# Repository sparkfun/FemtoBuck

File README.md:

FemtoBuck LED Driver
===================  
](https://cdn.sparkfun.com/assets/parts/1/1/2/1/0/13716-01.jpg) 
 
[*FemtoBuck LED Driver (COM-13716)*](https://www.sparkfun.com/products/13716) 

This breakout board allows you to dim a single high-power channel of LEDs from 0-330mA, or 0-660mA (depending on the setting of a solder jumper), at up to 36V. 
Dimming control can be either via PWM or via analog signal from 0-2.5V.

Repository Contents
-------------------
* **/Hardware** - All Eagle design files (.brd, .sch)
* **/Production** - Test bed files and production panel files

Documentation
--------------
* **[Hookup Guide](https://learn.sparkfun.com/tutorials/femtobuck-constant-current-led-driver-hookup-guide)** - Basic hookup guide for the FemtoBuck.
* **[SparkFun Fritzing repo](https://github.com/sparkfun/Fritzing_Parts)** - Fritzing diagrams for SparkFun products.
* **[SparkFun 3D Model repo](https://github.com/sparkfun/3D_Models)** - 3D models of SparkFun products. 

Product Versions
----------------
* [COM-13716](https://www.sparkfun.com/products/13716)- Version 1.2. Currently for sale. 
* [COM-12937] (https://www.sparkfun.com/products/12937)- Version 1.0. Retired. 

Version History
---------------
* [V_1.2](https://github.com/sparkfun/FemtoBuck/tree/V_1.2) - GitHub files for version 1.2. 
* [V_1.0](https://github.com/sparkfun/FemtoBuck/tree/v_10) - GitHub files for version 1.0. 

License Information
-------------------

This product is _**open source**_! 

Please review the LICENSE.md file for license information. 

If you have any questions or concerns on licensing, please contact techsupport@sparkfun.com.

Distributed as-is; no warranty is given.

- Your friends at SparkFun.

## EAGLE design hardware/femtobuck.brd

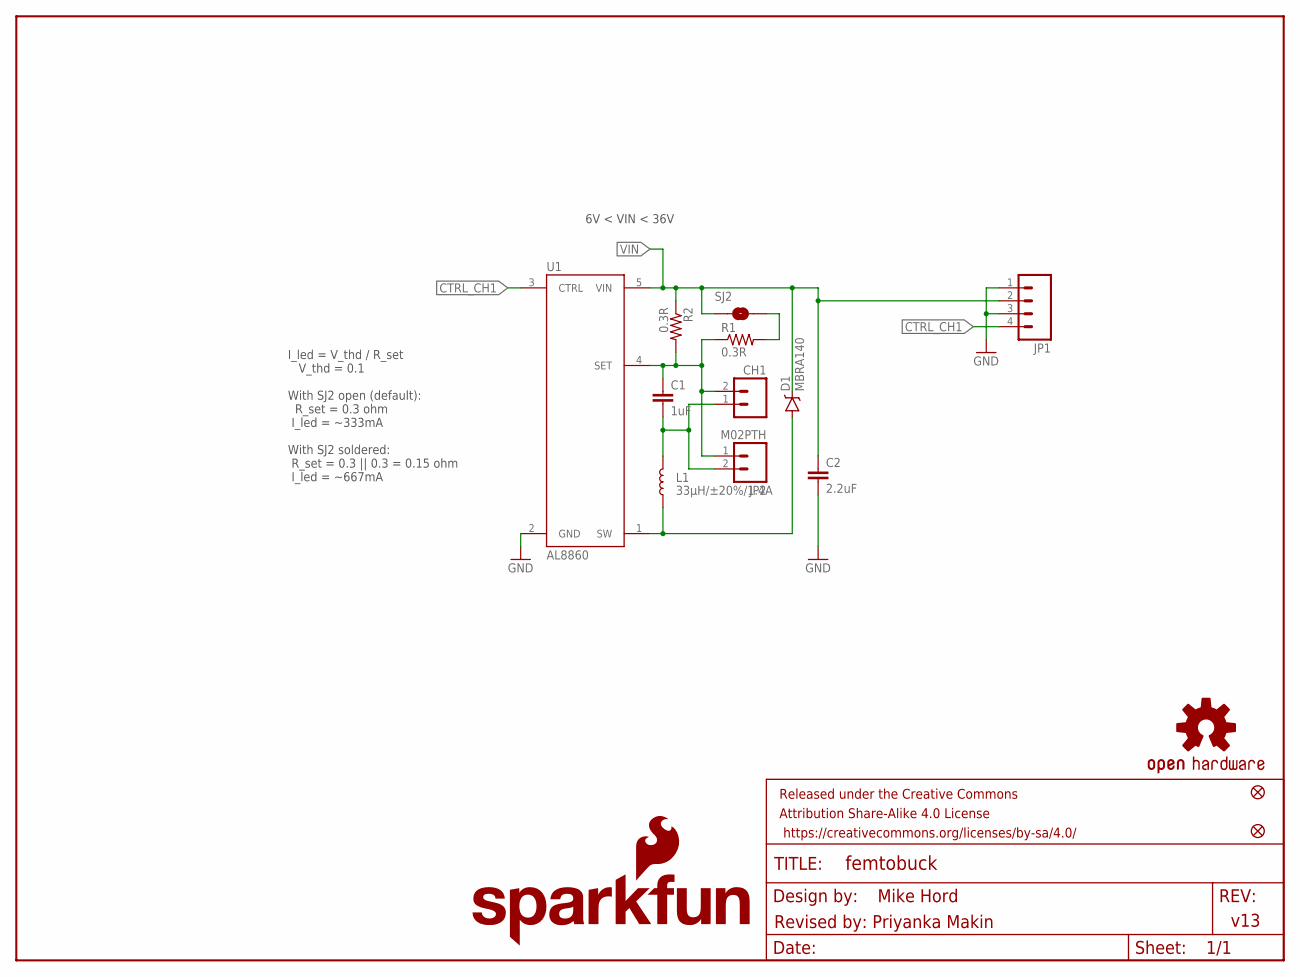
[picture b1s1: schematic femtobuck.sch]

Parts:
C1: 1uF; 1206-CAP
C2: 2.2uF; 1206-CAP
CH1: CONN_023.5MM_LOCK; SCREWTERMINAL-3.5MM-2_LOCK
D1: MBRA140; SMA-DIODE
FID1, FID2: FIDUCIAL1X2; FIDUCIAL-1X2
FRAME1: FRAME-LETTER; CREATIVE_COMMONS
JP1: M04PTH; 1X04
JP2: M02PTH; 1X02@1
L1: 33µH/±20%/1.4A; SRN6045
LOGO1: OSHW-LOGOS; OSHW-LOGO-S
LOGO2: SFE_LOGO_NAME_FLAME.1_INCH; SFE_LOGO_NAME_FLAME_.1
R1, R2: 0.3R; 0805
SJ2: NO Jumper; SMT-JUMPER_2_NO_NO-SILK
U1: AL8860; SOT23-5

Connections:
CTRL_CH1: JP1.4, U1.3 (CTRL)
GND: C2.2, JP1.1, JP1.3, U1.2 (GND)
unnamed: R1.2, SJ2.2
OUT+: C1.1, CH1.2, JP2.1, R1.1, R2.2, U1.4 (SET)
OUT-: C1.2, CH1.1, JP2.2, L1.2
SW: D1.A, L1.1, U1.1 (SW)
VIN: C2.1, D1.C, JP1.2, R2.1, SJ2.1, U1.5 (VIN)

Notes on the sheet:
I_led = V_thd / R_set V_thd = 0.1 With SJ2 open (default): R_set = 0.3 ohm I_led = ~333mA With SJ2 soldered: R_set = 0.3 || 0.3 = 0.15 ohm I_led = ~667mA
v13
Mike Hord
6V < VIN < 36V
Revised by: Priyanka Makin

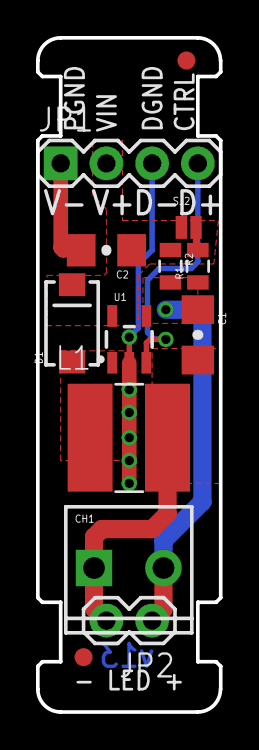
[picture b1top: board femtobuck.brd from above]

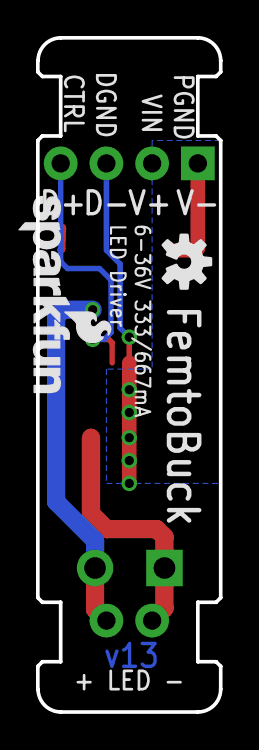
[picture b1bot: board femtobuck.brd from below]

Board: 2 copper layers, 10.2 x 37.5 mm, 16 parts (2 on the bottom side), 7 nets.

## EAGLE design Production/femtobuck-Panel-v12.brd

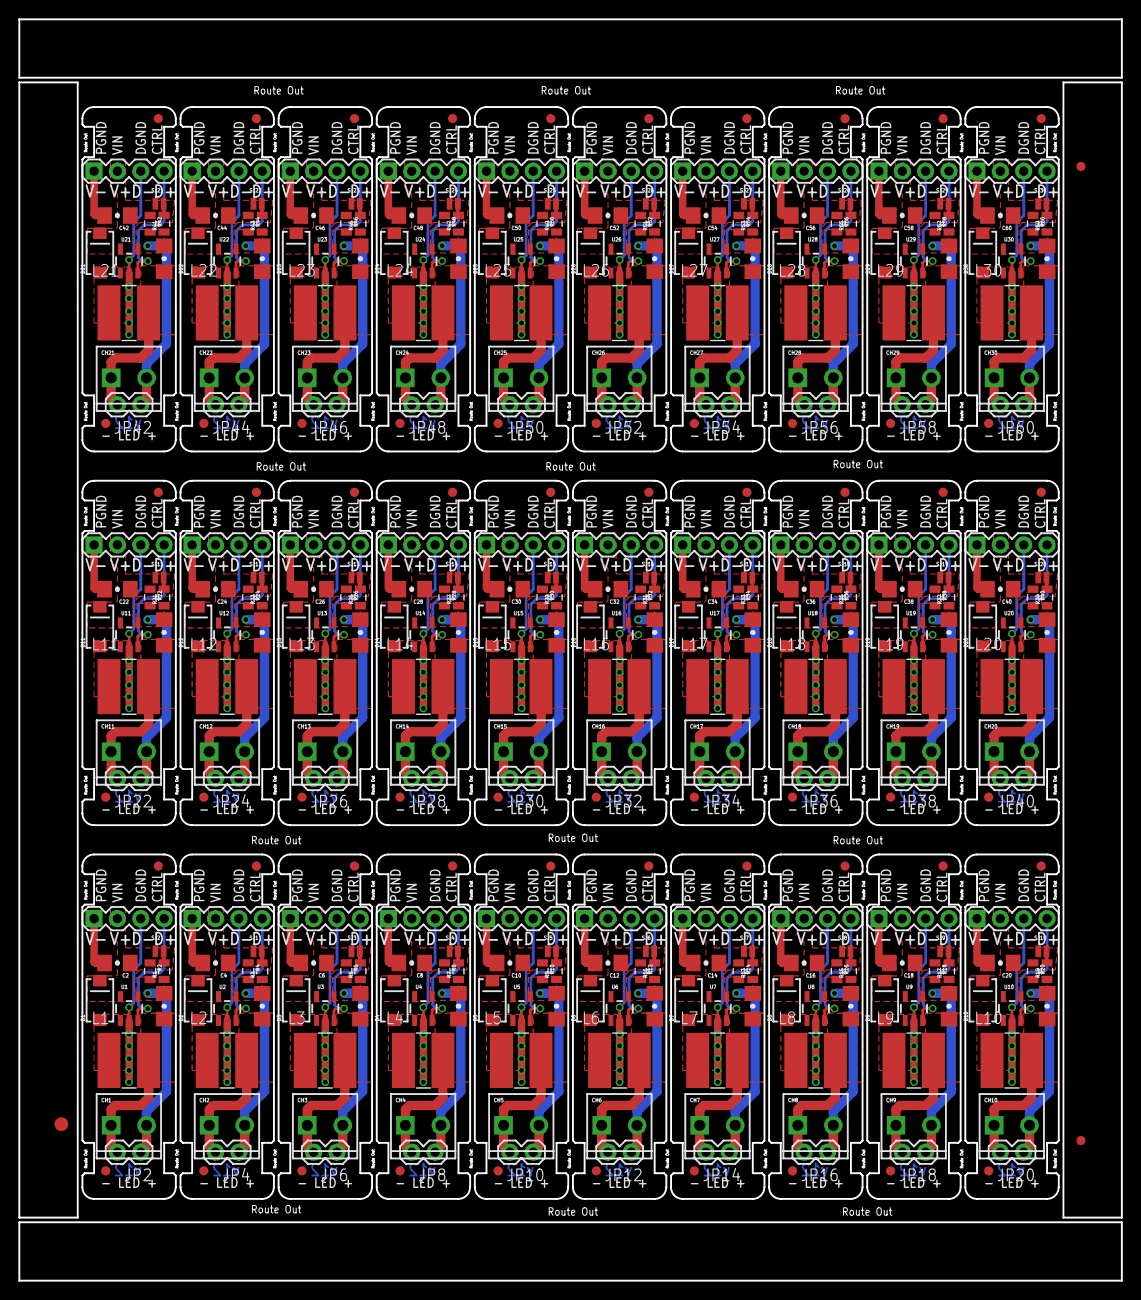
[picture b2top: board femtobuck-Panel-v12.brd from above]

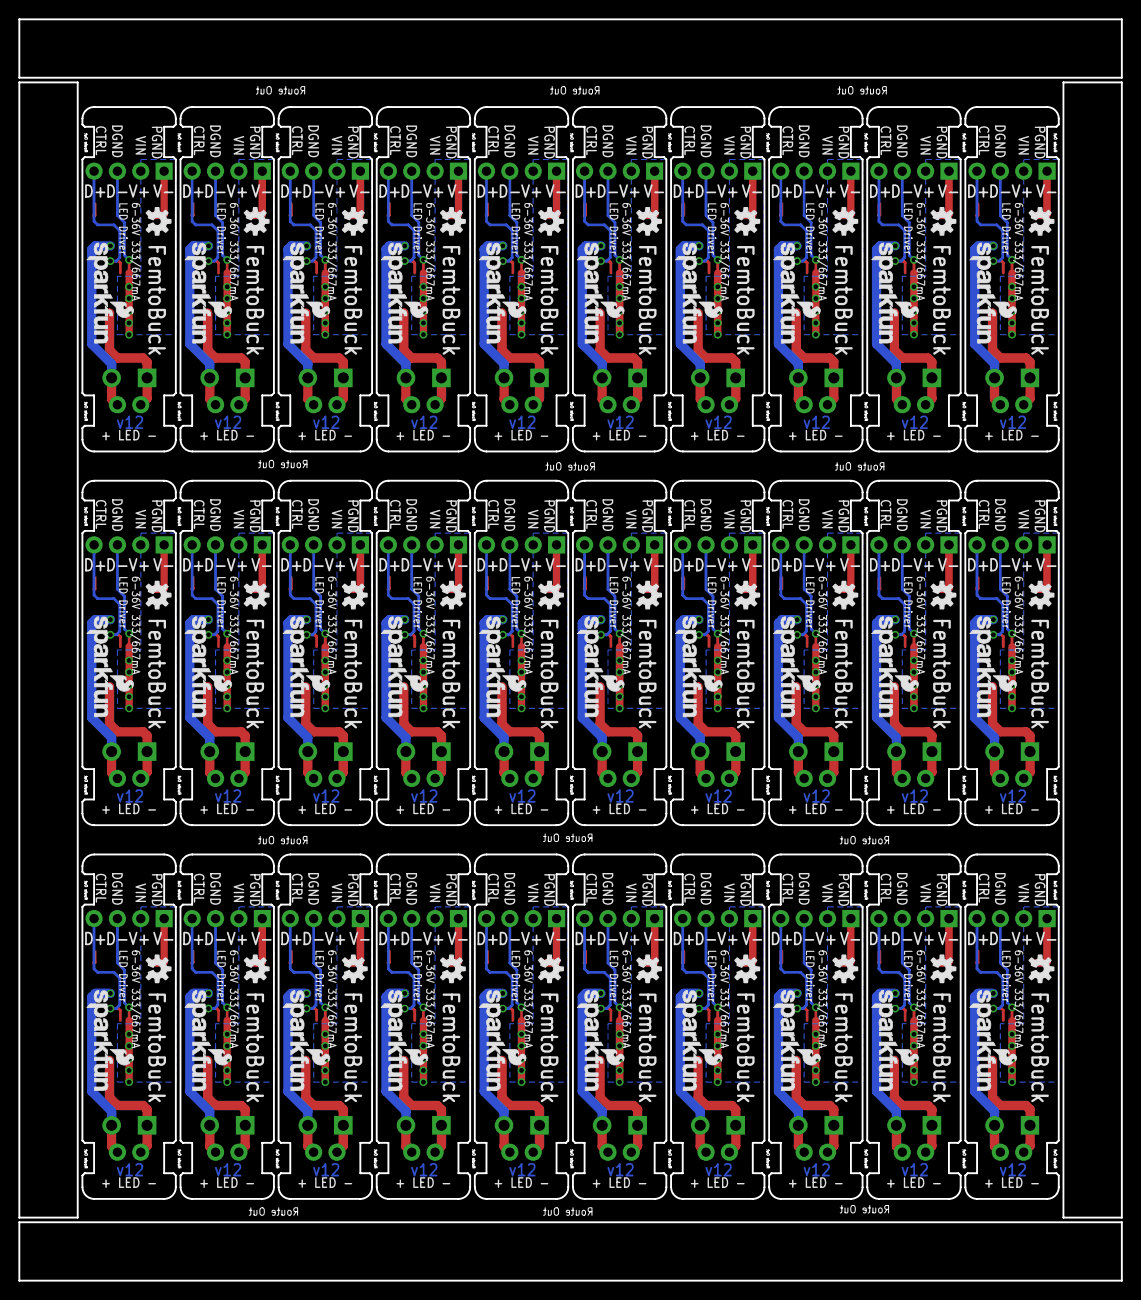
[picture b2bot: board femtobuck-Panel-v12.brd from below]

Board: 2 copper layers, 119.9 x 137.2 mm, 453 parts (60 on the bottom side), 210 nets.

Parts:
C1, C3, C5, C7, C9, C11, C13, C15, C17, C19, C21, C23, C25, C27, C29, C31, C33, C35, C37, C39, C41, C43, C45, C47, C49, C51, C53, C55, C57, C59: 1uF; 1206-CAP
C2, C4, C6, C8, C10, C12, C14, C16, C18, C20, C22, C24, C26, C28, C30, C32, C34, C36, C38, C40, C42, C44, C46, C48, C50, C52, C54, C56, C58, C60: 2.2uF; 1206-CAP
CH1, CH2, CH3, CH4, CH5, CH6, CH7, CH8, CH9, CH10, CH11, CH12, CH13, CH14, CH15, CH16, CH17, CH18, CH19, CH20, CH21, CH22, CH23, CH24, CH25, CH26, CH27, CH28, CH29, CH30: SCREWTERMINAL-3.5MM-2_LOCK
D1, D2, D3, D4, D5, D6, D7, D8, D9, D10, D11, D12, D13, D14, D15, D16, D17, D18, D19, D20, D21, D22, D23, D24, D25, D26, D27, D28, D29, D30: MBRA140; SMA-DIODE
E$1: FIDUCIAL-1.5X3
E$2, E$5: FIDUCIAL-1X2
FID1, FID2, FID3, FID4, FID5, FID6, FID7, FID8, FID9, FID10, FID11, FID12, FID13, FID14, FID15, FID16, FID17, FID18, FID19, FID20, FID21, FID22, FID23, FID24, FID25, FID26, FID27, FID28, FID29, FID30, FID31, FID32, FID33, FID34, FID35, FID36, FID37, FID38, FID39, FID40, FID41, FID42, FID43, FID44, FID45, FID46, FID47, FID48, FID49, FID50, FID51, FID52, FID53, FID54, FID55, FID56, FID57, FID58, FID59, FID60: FIDUCIAL1X2; FIDUCIAL-1X2
JP1, JP3, JP5, JP7, JP9, JP11, JP13, JP15, JP17, JP19, JP21, JP23, JP25, JP27, JP29, JP31, JP33, JP35, JP37, JP39, JP41, JP43, JP45, JP47, JP49, JP51, JP53, JP55, JP57, JP59: 1X04
JP2, JP4, JP6, JP8, JP10, JP12, JP14, JP16, JP18, JP20, JP22, JP24, JP26, JP28, JP30, JP32, JP34, JP36, JP38, JP40, JP42, JP44, JP46, JP48, JP50, JP52, JP54, JP56, JP58, JP60: M02PTH; 1X02
L1, L2, L3, L4, L5, L6, L7, L8, L9, L10, L11, L12, L13, L14, L15, L16, L17, L18, L19, L20, L21, L22, L23, L24, L25, L26, L27, L28, L29, L30: 33uH; SRN6045
LOGO1, LOGO3, LOGO5, LOGO7, LOGO9, LOGO11, LOGO13, LOGO15, LOGO17, LOGO19, LOGO21, LOGO23, LOGO25, LOGO27, LOGO29, LOGO31, LOGO33, LOGO35, LOGO37, LOGO39, LOGO41, LOGO43, LOGO45, LOGO47, LOGO49, LOGO51, LOGO53, LOGO55, LOGO57, LOGO59: OSHW-LOGOS; OSHW-LOGO-S
LOGO2, LOGO4, LOGO6, LOGO8, LOGO10, LOGO12, LOGO14, LOGO16, LOGO18, LOGO20, LOGO22, LOGO24, LOGO26, LOGO28, LOGO30, LOGO32, LOGO34, LOGO36, LOGO38, LOGO40, LOGO42, LOGO44, LOGO46, LOGO48, LOGO50, LOGO52, LOGO54, LOGO56, LOGO58, LOGO60: SFE_LOGO_NAME_FLAME.1_INCH; SFE_LOGO_NAME_FLAME_.1
R1, R2, R3, R4, R5, R6, R7, R8, R9, R10, R11, R12, R13, R14, R15, R16, R17, R18, R19, R20, R21, R22, R23, R24, R25, R26, R27, R28, R29, R30, R31, R32, R33, R34, R35, R36, R37, R38, R39, R40, R41, R42, R43, R44, R45, R46, R47, R48, R49, R50, R51, R52, R53, R54, R55, R56, R57, R58, R59, R60: 0.3R; 0805
SJ1, SJ2, SJ3, SJ4, SJ5, SJ6, SJ7, SJ8, SJ9, SJ10, SJ11, SJ12, SJ13, SJ14, SJ15, SJ16, SJ17, SJ18, SJ19, SJ20, SJ21, SJ22, SJ23, SJ24, SJ25, SJ26, SJ27, SJ28, SJ29, SJ30: NO Jumper; PAD-JUMPER-2-NO_NO_SILK
U1, U2, U3, U4, U5, U6, U7, U8, U9, U10, U11, U12, U13, U14, U15, U16, U17, U18, U19, U20, U21, U22, U23, U24, U25, U26, U27, U28, U29, U30: AL8805; SOT23-5

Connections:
CTRL_CH1: JP1.4, U1.3
CTRL_CH2: JP3.4, U2.3
CTRL_CH3: JP5.4, U3.3
CTRL_CH4: JP7.4, U4.3
CTRL_CH5: JP9.4, U5.3
CTRL_CH6: JP11.4, U6.3
CTRL_CH7: JP13.4, U7.3
CTRL_CH8: JP15.4, U8.3
CTRL_CH9: JP17.4, U9.3
CTRL_CH10: JP19.4, U10.3
CTRL_CH11: JP21.4, U11.3
CTRL_CH12: JP23.4, U12.3
CTRL_CH13: JP25.4, U13.3
CTRL_CH14: JP27.4, U14.3
CTRL_CH15: JP29.4, U15.3
CTRL_CH16: JP31.4, U16.3
CTRL_CH17: JP33.4, U17.3
CTRL_CH18: JP35.4, U18.3
CTRL_CH19: JP37.4, U19.3
CTRL_CH20: JP39.4, U20.3
CTRL_CH21: JP41.4, U21.3
CTRL_CH22: JP43.4, U22.3
CTRL_CH23: JP45.4, U23.3
CTRL_CH24: JP47.4, U24.3
CTRL_CH25: JP49.4, U25.3
CTRL_CH26: JP51.4, U26.3
CTRL_CH27: JP53.4, U27.3
CTRL_CH28: JP55.4, U28.3
CTRL_CH29: JP57.4, U29.3
CTRL_CH30: JP59.4, U30.3
GND: C2.2, JP1.1, JP1.3, U1.2
GND1: C4.2, JP3.1, JP3.3, U2.2
GND2: C6.2, JP5.1, JP5.3, U3.2
GND3: C8.2, JP7.1, JP7.3, U4.2
GND4: C10.2, JP9.1, JP9.3, U5.2
GND5: C12.2, JP11.1, JP11.3, U6.2
GND6: C14.2, JP13.1, JP13.3, U7.2
GND7: C16.2, JP15.1, JP15.3, U8.2
GND8: C18.2, JP17.1, JP17.3, U9.2
GND9: C20.2, JP19.1, JP19.3, U10.2
GND10: C22.2, JP21.1, JP21.3, U11.2
GND11: C24.2, JP23.1, JP23.3, U12.2
GND12: C26.2, JP25.1, JP25.3, U13.2
GND13: C28.2, JP27.1, JP27.3, U14.2
GND14: C30.2, JP29.1, JP29.3, U15.2
GND15: C32.2, JP31.1, JP31.3, U16.2
GND16: C34.2, JP33.1, JP33.3, U17.2
GND17: C36.2, JP35.1, JP35.3, U18.2
GND18: C38.2, JP37.1, JP37.3, U19.2
GND19: C40.2, JP39.1, JP39.3, U20.2
GND20: C42.2, JP41.1, JP41.3, U21.2
GND21: C44.2, JP43.1, JP43.3, U22.2
GND22: C46.2, JP45.1, JP45.3, U23.2
GND23: C48.2, JP47.1, JP47.3, U24.2
GND24: C50.2, JP49.1, JP49.3, U25.2
GND25: C52.2, JP51.1, JP51.3, U26.2
GND26: C54.2, JP53.1, JP53.3, U27.2
GND27: C56.2, JP55.1, JP55.3, U28.2
GND28: C58.2, JP57.1, JP57.3, U29.2
GND29: C60.2, JP59.1, JP59.3, U30.2
unnamed: R1.2, SJ2.2
unnamed: R3.2, SJ1.2
unnamed: R5.2, SJ3.2
unnamed: R7.2, SJ4.2
unnamed: R9.2, SJ5.2
unnamed: R11.2, SJ6.2
unnamed: R13.2, SJ7.2
unnamed: R15.2, SJ8.2
unnamed: R17.2, SJ9.2
unnamed: R19.2, SJ10.2
unnamed: R21.2, SJ11.2
unnamed: R23.2, SJ12.2
unnamed: R25.2, SJ13.2
unnamed: R27.2, SJ14.2
unnamed: R29.2, SJ15.2
unnamed: R31.2, SJ16.2
unnamed: R33.2, SJ17.2
unnamed: R35.2, SJ18.2
unnamed: R37.2, SJ19.2
unnamed: R39.2, SJ20.2
unnamed: R41.2, SJ21.2
unnamed: R43.2, SJ22.2
unnamed: R45.2, SJ23.2
unnamed: R47.2, SJ24.2
unnamed: R49.2, SJ25.2
unnamed: R51.2, SJ26.2
unnamed: R53.2, SJ27.2
unnamed: R55.2, SJ28.2
unnamed: R57.2, SJ29.2
unnamed: R59.2, SJ30.2
OUT+: C1.1, CH1.2, JP2.1, R1.1, R2.2, U1.4
OUT+1: C3.1, CH2.2, JP4.1, R3.1, R4.2, U2.4
OUT+2: C5.1, CH3.2, JP6.1, R5.1, R6.2, U3.4
OUT+3: C7.1, CH4.2, JP8.1, R7.1, R8.2, U4.4
OUT+4: C9.1, CH5.2, JP10.1, R9.1, R10.2, U5.4
OUT+5: C11.1, CH6.2, JP12.1, R11.1, R12.2, U6.4
OUT+6: C13.1, CH7.2, JP14.1, R13.1, R14.2, U7.4
OUT+7: C15.1, CH8.2, JP16.1, R15.1, R16.2, U8.4
OUT+8: C17.1, CH9.2, JP18.1, R17.1, R18.2, U9.4
OUT+9: C19.1, CH10.2, JP20.1, R19.1, R20.2, U10.4
OUT+10: C21.1, CH11.2, JP22.1, R21.1, R22.2, U11.4
OUT+11: C23.1, CH12.2, JP24.1, R23.1, R24.2, U12.4
OUT+12: C25.1, CH13.2, JP26.1, R25.1, R26.2, U13.4
OUT+13: C27.1, CH14.2, JP28.1, R27.1, R28.2, U14.4
OUT+14: C29.1, CH15.2, JP30.1, R29.1, R30.2, U15.4
OUT+15: C31.1, CH16.2, JP32.1, R31.1, R32.2, U16.4
OUT+16: C33.1, CH17.2, JP34.1, R33.1, R34.2, U17.4
OUT+17: C35.1, CH18.2, JP36.1, R35.1, R36.2, U18.4
OUT+18: C37.1, CH19.2, JP38.1, R37.1, R38.2, U19.4
OUT+19: C39.1, CH20.2, JP40.1, R39.1, R40.2, U20.4
OUT+20: C41.1, CH21.2, JP42.1, R41.1, R42.2, U21.4
OUT+21: C43.1, CH22.2, JP44.1, R43.1, R44.2, U22.4
OUT+22: C45.1, CH23.2, JP46.1, R45.1, R46.2, U23.4
OUT+23: C47.1, CH24.2, JP48.1, R47.1, R48.2, U24.4
OUT+24: C49.1, CH25.2, JP50.1, R49.1, R50.2, U25.4
OUT+25: C51.1, CH26.2, JP52.1, R51.1, R52.2, U26.4
OUT+26: C53.1, CH27.2, JP54.1, R53.1, R54.2, U27.4
OUT+27: C55.1, CH28.2, JP56.1, R55.1, R56.2, U28.4
OUT+28: C57.1, CH29.2, JP58.1, R57.1, R58.2, U29.4
OUT+29: C59.1, CH30.2, JP60.1, R59.1, R60.2, U30.4
OUT-: C1.2, CH1.1, JP2.2, L1.2
OUT-1: C3.2, CH2.1, JP4.2, L2.2
OUT-2: C5.2, CH3.1, JP6.2, L3.2
OUT-3: C7.2, CH4.1, JP8.2, L4.2
OUT-4: C9.2, CH5.1, JP10.2, L5.2
OUT-5: C11.2, CH6.1, JP12.2, L6.2
OUT-6: C13.2, CH7.1, JP14.2, L7.2
OUT-7: C15.2, CH8.1, JP16.2, L8.2
OUT-8: C17.2, CH9.1, JP18.2, L9.2
OUT-9: C19.2, CH10.1, JP20.2, L10.2
OUT-10: C21.2, CH11.1, JP22.2, L11.2
OUT-11: C23.2, CH12.1, JP24.2, L12.2
OUT-12: C25.2, CH13.1, JP26.2, L13.2
OUT-13: C27.2, CH14.1, JP28.2, L14.2
OUT-14: C29.2, CH15.1, JP30.2, L15.2
OUT-15: C31.2, CH16.1, JP32.2, L16.2
OUT-16: C33.2, CH17.1, JP34.2, L17.2
OUT-17: C35.2, CH18.1, JP36.2, L18.2
OUT-18: C37.2, CH19.1, JP38.2, L19.2
OUT-19: C39.2, CH20.1, JP40.2, L20.2
OUT-20: C41.2, CH21.1, JP42.2, L21.2
OUT-21: C43.2, CH22.1, JP44.2, L22.2
OUT-22: C45.2, CH23.1, JP46.2, L23.2
OUT-23: C47.2, CH24.1, JP48.2, L24.2
OUT-24: C49.2, CH25.1, JP50.2, L25.2
OUT-25: C51.2, CH26.1, JP52.2, L26.2
OUT-26: C53.2, CH27.1, JP54.2, L27.2
OUT-27: C55.2, CH28.1, JP56.2, L28.2
OUT-28: C57.2, CH29.1, JP58.2, L29.2
OUT-29: C59.2, CH30.1, JP60.2, L30.2
SW: D1.A, L1.1, U1.1
SW1: D2.A, L2.1, U2.1
SW2: D3.A, L3.1, U3.1
SW3: D4.A, L4.1, U4.1
SW4: D5.A, L5.1, U5.1
SW5: D6.A, L6.1, U6.1
SW6: D7.A, L7.1, U7.1
SW7: D8.A, L8.1, U8.1
SW8: D9.A, L9.1, U9.1
SW9: D10.A, L10.1, U10.1
SW10: D11.A, L11.1, U11.1
SW11: D12.A, L12.1, U12.1
SW12: D13.A, L13.1, U13.1
SW13: D14.A, L14.1, U14.1
SW14: D15.A, L15.1, U15.1
SW15: D16.A, L16.1, U16.1
SW16: D17.A, L17.1, U17.1
SW17: D18.A, L18.1, U18.1
SW18: D19.A, L19.1, U19.1
SW19: D20.A, L20.1, U20.1
SW20: D21.A, L21.1, U21.1
SW21: D22.A, L22.1, U22.1
SW22: D23.A, L23.1, U23.1
SW23: D24.A, L24.1, U24.1
SW24: D25.A, L25.1, U25.1
SW25: D26.A, L26.1, U26.1
SW26: D27.A, L27.1, U27.1
SW27: D28.A, L28.1, U28.1
SW28: D29.A, L29.1, U29.1
SW29: D30.A, L30.1, U30.1
VIN: C2.1, D1.C, JP1.2, R2.1, SJ2.1, U1.5
VIN1: C4.1, D2.C, JP3.2, R4.1, SJ1.1, U2.5
VIN2: C6.1, D3.C, JP5.2, R6.1, SJ3.1, U3.5
VIN3: C8.1, D4.C, JP7.2, R8.1, SJ4.1, U4.5
VIN4: C10.1, D5.C, JP9.2, R10.1, SJ5.1, U5.5
VIN5: C12.1, D6.C, JP11.2, R12.1, SJ6.1, U6.5
VIN6: C14.1, D7.C, JP13.2, R14.1, SJ7.1, U7.5
VIN7: C16.1, D8.C, JP15.2, R16.1, SJ8.1, U8.5
VIN8: C18.1, D9.C, JP17.2, R18.1, SJ9.1, U9.5
VIN9: C20.1, D10.C, JP19.2, R20.1, SJ10.1, U10.5
VIN10: C22.1, D11.C, JP21.2, R22.1, SJ11.1, U11.5
VIN11: C24.1, D12.C, JP23.2, R24.1, SJ12.1, U12.5
VIN12: C26.1, D13.C, JP25.2, R26.1, SJ13.1, U13.5
VIN13: C28.1, D14.C, JP27.2, R28.1, SJ14.1, U14.5
VIN14: C30.1, D15.C, JP29.2, R30.1, SJ15.1, U15.5
VIN15: C32.1, D16.C, JP31.2, R32.1, SJ16.1, U16.5
VIN16: C34.1, D17.C, JP33.2, R34.1, SJ17.1, U17.5
VIN17: C36.1, D18.C, JP35.2, R36.1, SJ18.1, U18.5
VIN18: C38.1, D19.C, JP37.2, R38.1, SJ19.1, U19.5
VIN19: C40.1, D20.C, JP39.2, R40.1, SJ20.1, U20.5
VIN20: C42.1, D21.C, JP41.2, R42.1, SJ21.1, U21.5
VIN21: C44.1, D22.C, JP43.2, R44.1, SJ22.1, U22.5
VIN22: C46.1, D23.C, JP45.2, R46.1, SJ23.1, U23.5
VIN23: C48.1, D24.C, JP47.2, R48.1, SJ24.1, U24.5
VIN24: C50.1, D25.C, JP49.2, R50.1, SJ25.1, U25.5
VIN25: C52.1, D26.C, JP51.2, R52.1, SJ26.1, U26.5
VIN26: C54.1, D27.C, JP53.2, R54.1, SJ27.1, U27.5
VIN27: C56.1, D28.C, JP55.2, R56.1, SJ28.1, U28.5
VIN28: C58.1, D29.C, JP57.2, R58.1, SJ29.1, U29.5
VIN29: C60.1, D30.C, JP59.2, R60.1, SJ30.1, U30.5

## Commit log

2014-05-19 Incorporate changes from review
2014-06-18 Small updates for production
2014-06-19 added board fiducials
2014-06-19 created panel v10
2015-07-01 Added 2nd sense resistor, jumper
2015-07-07 Fixed changes from QC
2015-08-10 created panel v11
2015-08-11 Chg to 12, inc. line wid on logos
2015-08-12 created panel v12
2015-09-15 Updated readme; ready for merge upon release
2015-12-10 Updating README with version info, adding license file
2022-03-03 AL8805 Buck LED driver EOL, replace with AL8860
2022-03-03 Add files
    * New datasheet for AL8860
    * Zip folder of eagle files (v13)

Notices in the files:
parts and their libraries:
SparkFun-Aesthetics: Licensing: CC v3.0 Share-Alike You are welcome to use this library for commercial purposes.
SparkFun-Connectors: Licensing: Creative Commons ShareAlike 4.0 International - https://creativecommons.org/licenses/by-sa/4.0
SparkFun-Aesthetics: Released under the Creative Commons
